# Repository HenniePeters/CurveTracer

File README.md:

# CurveTracer  
A digital curve tracer using Arduino, with source code and binaries for Windows and Linux  
  
__<h2>This repository is a work in progress</h2>__  
11-jan-2022  
  
Used tools:  
&nbsp;&nbsp;&nbsp;&nbsp; Borland C++Builder 6.0  (Windows)  
&nbsp;&nbsp;&nbsp;&nbsp; Code::Blocks 20.03  (Linux)  
&nbsp;&nbsp;&nbsp;&nbsp; Arduino IDE 1.8.11  
&nbsp;&nbsp;&nbsp;&nbsp; LTSpice 17.0.32  
&nbsp;&nbsp;&nbsp;&nbsp; Eagle 7.7  

15-jan-2022  
  
A working prototype (Mk1):  

4-jul-2022  
  
I am working on the STM32 version. The PC software and source for Linux are available in the MK2 directories.  
I've changed the number of samples from 48 to 50. This rounds to a better number for the delay in microseconds.
I'am currently trying to find a way to publish the source for STM32Cube. The project is 37Mb in size. Not a good idea to post that on github entirely. Any ideas are welcome.  

The circuit connects to a clone of a nucleo board. Pin names are available in the schematic.

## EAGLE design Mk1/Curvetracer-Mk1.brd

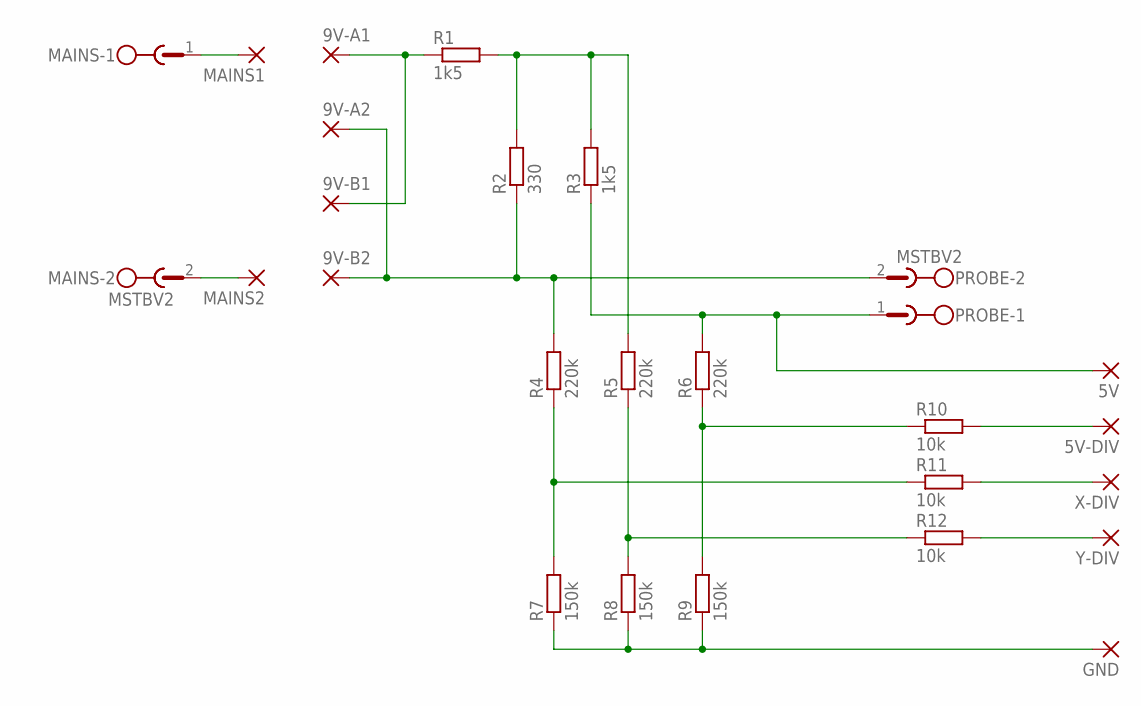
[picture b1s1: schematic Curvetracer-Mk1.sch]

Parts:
5V, 5V-DIV, 9V-A1, 9V-A2, 9V-B1, 9V-B2: 2,15/1,0
GND: 2,15/1,0
MAINS: MSTBV2
MAINS1, MAINS2: 2,15/1,0
PROBE: MSTBV2
R1, R3: 1k5; M0805
R2: 330; M0805
R4, R5, R6: 220k; M0805
R7, R8, R9: 150k; M0805
R10, R11, R12: 10k; M0805
X-DIV: 2,15/1,0
Y-DIV: 2,15/1,0

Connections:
unnamed: MAINS.1, MAINS1.1
unnamed: MAINS.2, MAINS2.1
unnamed: 9V-A1.1, 9V-B1.1, R1.1
unnamed: 9V-A2.1, 9V-B2.1, PROBE.2, R2.1, R4.2
unnamed: R1.2, R2.2, R3.2, R5.2
unnamed: 5V.1, PROBE.1, R3.1, R6.2
unnamed: R6.1, R9.2, R10.1
unnamed: R4.1, R7.2, R11.1
unnamed: R5.1, R8.2, R12.1
unnamed: GND.1, R7.1, R8.1, R9.1
unnamed: 5V-DIV.1, R10.2
unnamed: R11.2, X-DIV.1
unnamed: R12.2, Y-DIV.1

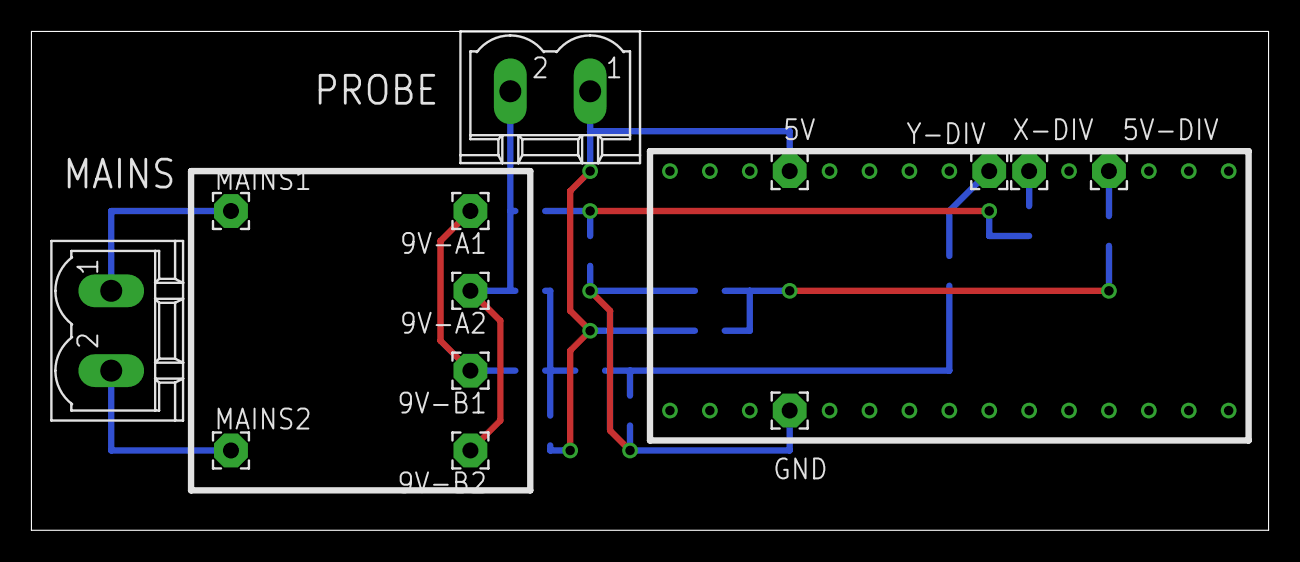
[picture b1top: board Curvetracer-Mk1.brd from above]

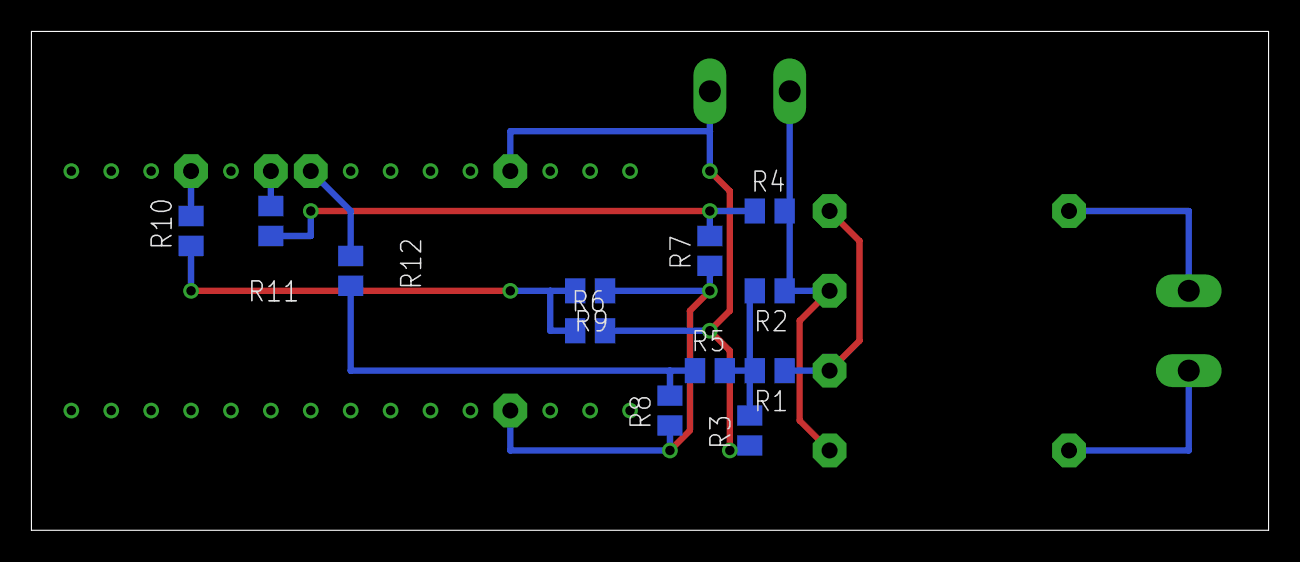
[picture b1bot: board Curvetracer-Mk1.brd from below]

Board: 2 copper layers, 78.7 x 31.8 mm, 25 parts (12 on the bottom side), 13 nets.

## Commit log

2022-11-17 Create LICENSE
